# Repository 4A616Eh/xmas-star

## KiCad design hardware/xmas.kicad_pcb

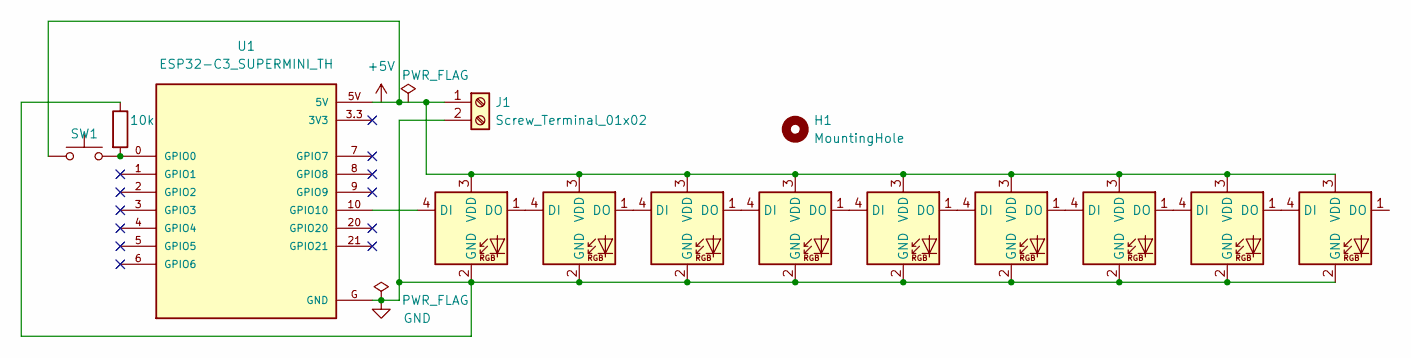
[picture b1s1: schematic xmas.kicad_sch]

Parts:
D1, D2, D3, D4, D5, D6, D7, D8, D9: APA-106-F5; LED_D5.0mm-4_RGB
H1: MountingHole; MountingHole_3.2mm_M3
J1: Screw_Terminal_01x02; TerminalBlock_Phoenix_MPT-0,5-2-2.54_1x02_P2.54mm_Horizontal
R1: 10k; R_Axial_DIN0411_L9.9mm_D3.6mm_P15.24mm_Horizontal
SW1: SW_Push; SW_PUSH_6mm
U1: ESP32-C3_SUPERMINI_TH; MODULE_ESP32-C3_SUPERMINI_TH

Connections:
GND: D1.2 (GND), D2.2 (GND), D3.2 (GND), D4.2 (GND), D5.2 (GND), D6.2 (GND), D7.2 (GND), D8.2 (GND), D9.2 (GND), J1.2, R1.1, U1.G (GND)
unnamed: D1.1 (DO), D2.4 (DI)
unnamed: D2.1 (DO), D3.4 (DI)
unnamed: D3.1 (DO), D4.4 (DI)
unnamed: D4.1 (DO), D5.4 (DI)
unnamed: D5.1 (DO), D6.4 (DI)
unnamed: D6.1 (DO), D7.4 (DI)
unnamed: D7.1 (DO), D8.4 (DI)
unnamed: D8.1 (DO), D9.4 (DI)
unnamed: R1.2, SW1.2, U1.0 (GPIO0)
unnamed: D1.3 (VDD), D2.3 (VDD), D3.3 (VDD), D4.3 (VDD), D5.3 (VDD), D6.3 (VDD), D7.3 (VDD), D8.3 (VDD), D9.3 (VDD), J1.1, SW1.1, U1.5V
unnamed: D1.4 (DI), U1.10 (GPIO10)

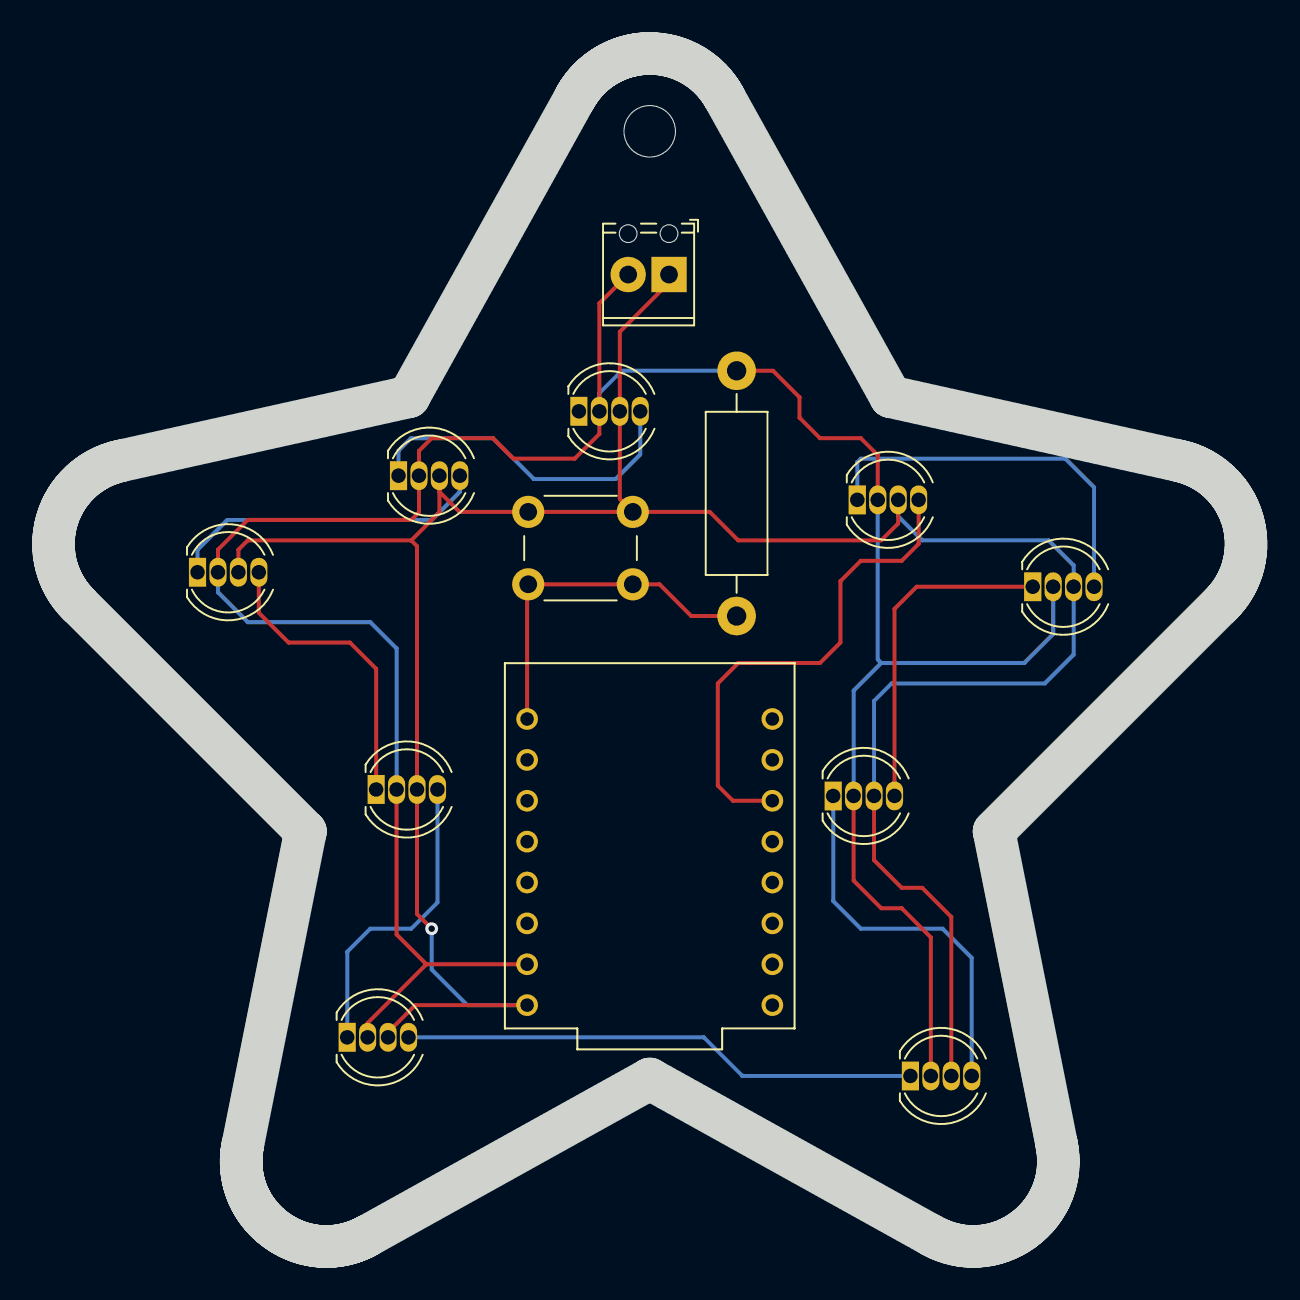
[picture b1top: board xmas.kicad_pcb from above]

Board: 2 copper layers, 74.1 x 74.1 mm, 14 parts (0 on the bottom side), 12 nets.

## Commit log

2025-11-21 example from FastLED lib - configured for xmas board
2025-11-21 Add pins_arduino.h
2025-11-21 Add hardware schematic + pcb
2025-11-22 Add pattern "xmasRedGreen"
2025-11-22 Improvements and Fixes: color order corrected! Debug messages can be disabled; Use of Random seed, pallete passed to animation function.
